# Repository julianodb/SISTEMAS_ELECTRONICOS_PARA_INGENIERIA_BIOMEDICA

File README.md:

#  Sistemas Electrónicos 2/2026
##### enfoque Ingeniería Biomédia

## Links

[uvirtual](https://uvirtual.usach.cl/moodle/course/view.php?id=52359): página oficial de la asignatura

[Clase de Tinkercad](https://www.tinkercad.com/joinclass/5XK7AATBK): para Laboratorios Online

[Falstad](https://www.falstad.com/circuit/): para Simulaciones de circuitos

## Horário Teoría
- Martes: 
    - bloque 5 (M5: 15:20 - 16:40): ED606
    - bloque 6 (M6: 16:55 - 18:15): ED606

## Horário Laboratório
- Jueves:
    - bloque 5 (J5: 15:20 - 16:40): Laboratorio de Electromedicina y Mediciones Fisiológicas
    - bloque 6 (J6: 16:55 - 18:15):  Laboratorio de Electromedicina y Mediciones Fisiológicas

## Profesor

- Juliano Dawid Barboza (juliano.dawid @usach.cl)

### Ayudante

- 

## Resultados de Aprendizaje

Al término de la asignatura, el estudiante será capaz de integrar los conocimientos de electrónica analógica para **analizar, diseñar, fabricar, probar y simular** circuitos electrónicos, con un énfasis especial en su aplicación en el ámbito de la ingeniería biomédica. Específicamente, el estudiante desarrollará las competencias necesarias para:

*   **Analizar** circuitos complejos identificando el comportamiento de componentes pasivos y semiconductores (resistores, capacitores, diodos, transistores, amplificadores operacionales).
*   **Diseñar** soluciones electrónicas funcionales para necesidades biomédicas, utilizando técnicas de filtrado, amplificación y regulación.
*   **Fabricar** prototipos electrónicos comprobando su funcionamiento mediante pruebas de concepto.
*   **Probar y experimentar** con instrumentación real, comprendiendo las limitaciones físicas del trabajo de laboratorio.
*   **Simular** circuitos utilizando herramientas digitales para validar el diseño previo a la implementación.

## Evaluaciones

Las notas de todas las evaluaciones serán redondeadas a una casa decimal hacia arriba (ej. 4.51 se redondea a 4.6):

$$ Nota Redondeada = \frac{\lceil 10\  Nota Original \rceil}{10}$$

Las evaluaciones se estructuran según las capacidades desarrolladas:

| Capacidad | Evaluación | Cantidad |
| :--- | :--- | :---: |
| **Analizar** | Pruebas escritas | 3 |
| **Diseñar** | Trabajos de diseño electrónico | 7 |
| **Fabricar** | Talleres de fabricación | 3 |
| **Probar** | Laboratorios presenciales | 7 |
| **Simular** | Laboratorios online | 6 |

### Teoría
La nota de teoría está compuesta por 60% del promedio simple de las evaluaciones escritas, 20% del promedio simple de los trabajos y 20% del promedio simple de los talleres de fabricación.

$$ Promedio Teoría = 0.6\sum_{i=1}^{np} \frac{P_i}{np} + 0.2\sum_{j=1}^{nt} \frac{T_j}{nt} + 0.2\sum_{k=1}^{nf} \frac{F_k}{nf} $$

Donde $P_i$ es la Prueba Escrita "i", $T_j$ es el trabajo de diseño "j", y $F_k$ es el taller de fabricación "k". Están planificados $np=3$ pruebas escritas, $nt=7$ trabajos de diseño y $nf=3$ talleres de fabricación.

Cada trabajo de diseño tiene una fecha y hora maxima de entrega. En el caso de que se entregue el trabajo con hasta 24 horas de atraso, se descuenta la mitad de la nota (máxima nota posible 4.0). Si se entrega el trabajo con más de 24 horas de atraso, se considera una nota 1.0.

El sistema de evaluación contempla, además, una Prueba Optativa Recuperativa (POR)

- Si el/la estudiante en el promedio final obtiene una nota menor a 4.0, pero mayor o igual a 3.0, puede optar a una POR.
- La POR reemplaza la peor nota de las 3 pruebas escritas.
- El contenido de la POR es toda la materia

$$ Promedio Teoría = 0.6\frac{ \sum{P_i} + POR - min\{P_i\}}{np} + 0.2\sum_{j=1}^{nt} \frac{T_j}{nt} + 0.2\sum_{k=1}^{nf} \frac{F_k}{nf}  $$

Si el Promedio Teoría es menor a 4.0, el/la estudiante reprueba la parte teórica de la asignatura.

#### Asistencia a Clases

Se exige un mínimo de 75 % de asistencia a clases presenciales. Una asistencia inferior al 75 % sin justificaciones ante docencia causa reprobación automatica de la parte teórica de la asignatura, con una nota 3.5 .

Están planificadas 20 clases de teoría, impartidas 2 por día en 10 días distintos, por lo que el número maximo de ausencias injustificadas es de 2 días.

### Laboratorio

El desarrollo del laboratorio estará en función a experiencias presenciales, online y talleres de fabricación. Las experiencias presenciales corresponderán a guías que deberán ser desarrolladas en clases, y cuyo informe deberá ser entregado al finalizar la sesión. Las experiencias online serán desarrolladas con la plataforma tinkercad, y serán evaluadas a través de cuestionarios en uvirtual. Los talleres de fabricación se desarrollan de forma similar a los laboratorios presenciales, con una guía que estipula un objetivo que debe ser alcanzado durante el horario de la clase, y cuyo resultado debe ser demonstrado al profesor antes de finalizar la sesión.

Las ponderaciones para la evaluación de laboratorio serán 60% del promedio simple de las experiencias presenciales, 20% del promedio simple de las experiencias online y 20% de los talleres de fabricación:

$$ Promedio Laboratorio = 0.6\sum_{i=1}^{nl} \frac {Lp_i}{nl} + 0.2\sum_{j=1}^{no} \frac {Lo_j}{no} + 0.2\sum_{k=1}^{nf} \frac{F_k}{nf} $$

Donde $Lp_i$ son las notas de las experiencias de laboratorio presenciales, $Lo_j$ son las notas de las experiencias de laboratorio online y $F_k$ las notas de los talleres de fabricación. Están planificados $nl=7$ actividades de laboratorio presenciales, $no=6$ actividades online y $nf=3$ talleres de fabricación durante el semestre.

Si el Promedio Laboratorio es menor a 4.0, el/la estudiante reprueba la parte de laboratorio de la asignatura.

#### Asistencia a Laboratorios

La inasistencia al laboratorio presencial deberá ser justificada ante docencia, quien informará a los profesores sobre la justificación de ésta. En caso de inasistencia justificada, la actividad de recuperación será informada caso a caso.

La inasistencia INJUSTIFICADA a un laboratorio causa reprobación automática de la parte de laboratorio de la asignatura, con una nota 3.5 .

### Promedio final y aprobación

En el caso de que el/la estudiante repruebe apenas teoría o apenas laboratorio, tendrá que cursar solamente la parte reprobada en el semestre siguiente en que se dicte la asignatura.

El promedio final de la asignatura se calcula como:

$$ Promedio Final = 0.7\ Promedio Teoría + 0.3\ Promedio Laboratorio  $$

Se considera redondeo convencional con una casa decimal para el promedio final (entre 0.01 y 0.04 se redondea hacia abajo: 0.0; y entre 0.05 y 0.09 se redondea hacia arriba: 0.1).

Respecto a las demás reglas de docencia, este curso se adscribe a las [DIRECTRICES DOCENCIA ING. CIVIL BIOMEDICA 2024](https://ingenieriabiomedica.usach.cl/sites/ing-civil-biomedica/files/directrices_docencia_ing._civil_biomedica_2024.pdf).

## Bibliografia
- Boylestad, R. & Nashelsky, L. (2009). Electrónica: Teoría de circuitos y dispositivos electrónicos (10ma.ed.).México: Prentice Hall.
- Millman, J. & Grabel, A. (2001). Microelectronics. MC GRAW HILL INDIA; 2nd edition.

## Programa de Actividades

[Calendario](CALENDAR.md)

### Clases

1. [Introducción y contexto](/teoria/01_Introduccion.md)
2. [Amplificadores](/teoria/02_amplifiers.md)
3. [Amplificadores operacionales I](/teoria/03_opamp.md)
4. [Amplificadores operacionales II](/teoria/04_opamp_II.md)
5. [Respuesta transitoria y estado estacionario](/teoria/05_transient.md)
6. [Amplificadores operacionales III](/teoria/06_opamp_III.md)
7. [Diodos y aplicaciones I](/teoria/07_diodes.md)
8. [Diodos y aplicaciones II](/teoria/08_diodes_II.md)
9. [MOSFET I](/teoria/09_MOSFET_I.md)
10. [MOSFET II](/teoria/10_MOSFET_II.md)
11. [Reguladores de voltaje (parte I)](/teoria/11_12_voltage_regulators.md)
12. [Reguladores de voltaje (parte II)](/teoria/11_12_voltage_regulators.md)
13. [Reguladores de voltaje II](/teoria/13_voltage_regulators_II.md)
14. [Semiconductores](/teoria/14_semiconductors.md)
15. [Respuesta en frecuencia y filtros I](/teoria/15_frec.md)
16. [Respuesta en frecuencia y filtros II](/teoria/16_frec_II.md)
17. [Respuesta en frecuencia y filtros III](/teoria/17_frec_III.md)
18. [Osciladores](/teoria/18_oscilators.md)
19. [Multivibradores I](/teoria/19_multivibrators.md)
20. [Multivibradores II](/teoria/20_multivibrators_II.md)

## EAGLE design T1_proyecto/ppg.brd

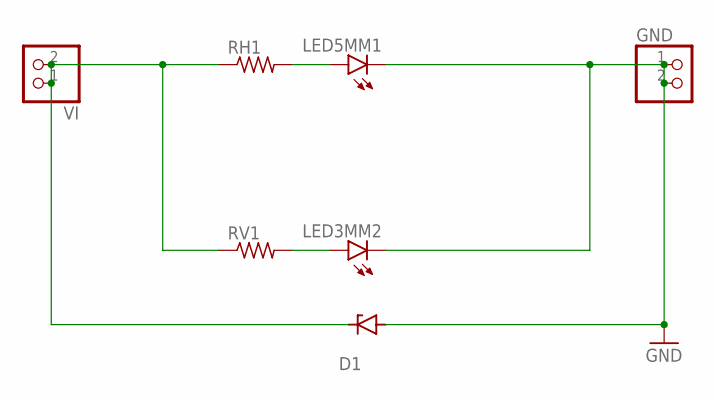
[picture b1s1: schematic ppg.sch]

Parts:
D1: DO41Z10
GND: 1X02
LED3MM2: LED3MM
LED5MM1: LED5MM
RH1: R-US_VMTA55; VMTA55
RV1: R-US_0207/5V; 0207/5V
VI: 1X02

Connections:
GND: D1.A, GND.1, GND.2, LED3MM2.K (C), LED5MM1.K (C)
unnamed: LED5MM1.A, RH1.2
unnamed: LED3MM2.A, RV1.2
unnamed: D1.C, RH1.1, RV1.1, VI.1, VI.2

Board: 2 copper layers, 7 parts (2 on the bottom side), 4 nets, no tracks yet.

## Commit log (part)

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2025-08-08 renumber L8_vreg
2025-08-08 renumber L9_multivibrators
2025-08-08 adapt L8 to 2025/02
2025-08-08 add LX_fabs labs
2025-08-08 add LA to calendar list
2025-08-08 slight adjustment to subtitle
2025-08-17 Add En ti calendar
2025-08-17 Update number of evaluations
2025-08-17 Update 01_Introduccion to 02/2025
2025-08-17 Add stethoscope description
2025-08-17 Add stethoscope image
2025-08-18 update TX and notas to 2/2025
2025-08-18 start cleanup of T1 for 02/2025
2025-08-18 add potentiometer to things to discuss in 02
2025-08-18 add questions for T1
2025-08-18 add lm386_package image
2025-08-18 finalize T1.3 and add images
2025-08-18 make minor adjustments to T1
2025-08-18 improve T1 readability
2025-08-18 increase image 3 width
2025-08-18 add potentiometer image to 01
2025-08-19 add missing images
2025-08-19 finalize 02
2025-08-19 minor improvements to 02
2025-08-19 add 02/2025 image
2025-08-21 slim down image in 02
2025-08-21 add \Omega symbol to 1M resistance
2025-08-21 initial changes on T2 for 02/2025
2025-08-22 Fix bibliography reference
2025-08-22 Update bibliography
2025-08-22 Add cap values
2025-08-22 update L2
2025-08-22 update 03 and 04
2025-08-24 make progress with T2
2025-08-26 finalize T2
2025-08-26 improve readability and add last details on T2.11
2025-08-26 add one more question to T2
2025-08-26 minor adjustments to T2
2025-08-26 improve images in 04
2025-08-26 change T2 semester
2025-08-26 add non_inverting amplifier
2025-08-30 add some details to 05
2025-08-30 add unit_response img
2025-08-30 make progress with 05
2025-08-31 add 05.7
2025-08-31 start modifying P1 and P2
2025-08-31 finalize 05
2025-08-31 finalize P1.3 and .4
2025-08-31 finalize P1
2025-09-01 finalize P1_preview
2025-09-01 fiz numbering in P1
2025-09-01 add one more formula
2025-09-01 modify P1 values a bit
2025-09-01 remove toc and add 1 more question to 05
2025-09-01 add a couple of examples to 06
2025-09-01 adapt calendar
2025-09-02 rename semiconductors
2025-09-02 add image for L3
2025-09-03 add P1_preview_answers for 02/2025
2025-09-04 start adapting T3 to 2025/02
2025-09-07 add all questions in T3
2025-09-07 add pmosfet MPN in T6
2025-09-07 small readability improvement to L3
2025-09-07 adjust image size
2025-09-07 adjust grades in T3
2025-09-08 small update to L3
2025-09-08 add P1_pauta
2025-09-08 add 1.2
2025-09-08 add answers to second question
2025-09-08 small label fixes
2025-09-09 add P1_pauta.3 and .4 (partial)
2025-09-10 finaliza P1_pauta
2025-09-11 distribute L3_fab_I_intro content to L6 as well
2025-09-12 add tips
2025-09-16 small fix to P1_pauta calculation
2025-09-22 add a couple more comments to L3
2025-09-22 add tips to advance fabrication
2025-09-25 finalize L4
2025-09-25 add L4 imgs
2025-09-25 add more notes to L3
2025-09-25 add more details to 07
2025-09-28 initial changes to T4 for 2025/02
2025-09-28 change oscilators class to 09
2025-09-28 change diodes to 10
2025-09-28 change diodes to 11
2025-09-28 change frec_III to 12
2025-09-28 fix numbering of classes
2025-09-28 initial draft of 07
2025-09-29 finalize T4
2025-09-29 fix img sizes
2025-09-29 minor adjustments to T4
2025-09-29 remove old subject from calendar
2025-09-29 finalize 07
2025-09-29 finalize 08
2025-09-29 fix escaping
2025-09-29 improve some formatting
2025-09-29 fix typo
2025-09-29 fix another typo
2025-09-29 add 07 imgs
2025-09-30 add a couple more restrictions to last question
2025-10-02 initial adjustments due to paro
2025-10-02 move L6 to end of semester
2025-10-06 add more ideas to P2
2025-10-06 add class_07.m
2025-10-06 adjust calendar due to paro
2025-10-10 improve readability in 09
2025-10-10 add full questions for P2
2025-10-16 adapt CALENDAR to more PP 15/10
2025-10-16 add january to CALENDAR
2025-10-16 modify P2 transfer function
2025-10-21 finalize P2
2025-10-21 adjust scores and component numbers
2025-10-21 modify P2_preview to 2025/02
2025-10-21 fix transfer function
2025-10-22 improve P2.2 question
2025-10-24 add class_09.m
2025-10-24 update 09
2025-10-24 update 10
2025-10-26 re-adapt calendar due to PARO
2025-10-26 adapt T5 to 2025/02
2025-10-27 start writing T5.2
2025-10-28 make progress with T5.2
2025-11-03 add T5_envelope_waveform.png
2025-11-03 finalize T5.2
2025-11-05 add T5.3
2025-11-05 update CALENDAR due to continuation of PARO
2025-11-11 tentative calendar if paro ends next week
2025-11-11 finalize T5
2025-11-11 final adjustments to T5
2025-11-11 change week #
2025-11-11 slight improvements to L5 wording
2025-11-11 add L6 draft
2025-11-12 add BOM to T5
2025-11-12 reorder L6 andd add img
2025-11-12 add a couple more details to L6
2025-11-17 add March and tentative dates for end of PARO
2025-11-17 fix formatting
2025-11-18 fix proposed TT
2025-11-18 add online classes on 30/12
2025-11-18 add bridge days
2025-11-24 update CALENDAR with last week of PARO
2025-11-24 add more details to L6
2025-11-27 final adjustments before printing
2025-11-30 update week #
2025-11-30 change T5 delivery date
2025-12-01 update P2_preview
2025-12-01 minor adjustments to P2
2025-12-08 small updates to P2
2025-12-11 add answers to P2_preview
2025-12-16 add questions to P2_pauta
2025-12-16 add some answers
2025-12-16 add more answers
2025-12-16 small changes on formulas
2025-12-16 change 13 title
2025-12-16 small clarification to L6
2025-12-16 invert March Labs
2025-12-16 initial draft for 13
2025-12-17 a bit more progress to P2_pauta
2025-12-17 add more details to 13
2025-12-18 finalize T6 questions
2025-12-18 update 13 and 14
2025-12-18 add scoring to T6
2025-12-19 finalize 13
2025-12-19 fix small typo on T6
2025-12-21 add cancel package via helper
2025-12-21 finalize P2_pauta
2025-12-23 finalize L7
2025-12-26 finalize 14
2025-12-26 final adjustments to L7
2025-12-26 small adjustments to 14
2025-12-27 small improvement to 14
2025-12-27 add missing img
2025-12-28 fix typos in 16
2025-12-28 make progress with 15
2025-12-29 add more details to 15
2025-12-29 add more details to 16
2025-12-30 finalize 15
2025-12-30 add details about rizo to 15
2025-12-30 add annotated images to 15
2025-12-30 add recommended exercises
2025-12-30 add imgs to 16
2025-12-30 small fix to imgs in 16
2025-12-30 add T7 for 2025/02
2025-12-31 slight change to P2_pauta.1 scoring
2026-01-01 small fix to P2_pauta img
2026-01-01 change * to \times
2026-01-06 finalize T8
2026-01-06 small fixes
2026-01-10 small change to 19
2026-01-10 add more stuff to P3_formulas
2026-01-10 switch labs 8 and 9 order
2026-01-10 add new imgs for 19
2026-01-10 remove intro to L8
2026-01-10 initial calendar changes for 2026/01
2026-01-10 add more detaisl to calendar
2026-01-11 add POR
2026-01-11 fix lab # after switch
2026-01-13 finalize LA
2026-01-15 add more details to LA
2026-01-15 small adjustments to L8
2026-01-27 move P3 due to "back from recess" restriction
2026-01-27 add 2 options for L9
2026-01-31 change p3 date
2026-01-31 finalize L9
2026-02-05 add a couple more formulas to P3
2026-02-22 reorder labs
2026-02-22 reorder classes
2026-03-15 final changes to sthetoscope.diy
2026-03-15 rename L9 to L7
2026-03-19 smalla djustments
2026-03-19 adjust to 2026/01
2026-03-20 update notas image
2026-03-20 adjust L1 to 2026/01
2026-03-20 update sto 01 and 02
2026-03-20 update TX
2026-03-20 more about work
2026-03-24 finalize 01
2026-03-24 update uvirtual link
2026-04-01 add 01_aplicaciones
2026-04-01 add T1
2026-04-05 initialize T2
2026-04-05 add T2 questions
2026-04-06 add imgs & switch to diff voltages
2026-04-06 change zener img
2026-04-07 make images bigger
2026-04-07 add new questions for L2
2026-04-07 fix question number
2026-04-13 initialize T3
2026-04-13 change zener input voltages so it doesn heat up as much
2026-04-13 finalize T3
2026-04-13 fix small typo
2026-04-13 move T4
2026-04-14 minor rewording and table adjustments
2026-04-14 initialize T4
2026-04-15 small adjustment to 06 regarding mosfet instead of bjt
2026-04-15 update tasks delivery dates
2026-04-21 initial draft of P1
2026-04-21 modify P1_preview
2026-04-23 finalize L3
2026-04-23 add a couple more details to L3
2026-04-23 update L3 to 2026/01
2026-04-24 finalize P1.1
2026-05-04 final P1 adjustments
2026-05-04 add P1_preciew_answers
2026-05-05 add initial changes of T5 for 2026/01
2026-05-05 minor wording improvements
2026-05-07 add P1.1
2026-05-08 add P1.2
2026-05-08 add P1.3
2026-05-08 add P1.4
2026-05-08 add scores
2026-05-08 fix score
2026-05-12 initialize T6
2026-05-12 change T6 delviery date
2026-05-12 advance T6, only missing images now
2026-05-12 finalize T6 imgs
2026-05-12 recalendarizacion
2026-05-12 final changes to T6
2026-05-12 minor calculation fix
2026-05-14 revert recalendarizacion
2026-05-14 recalendarizacion 2
2026-05-14 fix small typos and improve readability
2026-05-19 adapt L4 to 2026/01
2026-05-27 add map of electronics image
2026-06-16 initial P2 proposal
2026-06-16 add 1 more formula
2026-06-18 finalize P2_preview
2026-06-23 fix R values on P2_preview
